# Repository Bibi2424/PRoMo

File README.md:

# PRoMo

## "Plateforme pour la Robotique Mobile"

### Mobile Robotic Plateform

This project is about creating a mobile robot from scratch.
There are four major parts in this project :

- Mechanics : Build a differential drive plateform with two DC motors with encoders. The different components must be build with Laser cutting and 3D printing (from low cost websites).
			
- Electronics : Create a main board based on a STM32F4 microcontroller with many components like motors, sensors, actuators, RF transmitters...
			
- Firmware : This can go two ways:
	- Provide a sets of high level librairies for controlling a sets of sensors and actuators and example projects, 
	- Give the code as is but with a performant way of interfacing with it (serial communication)

- Documentation : All the informations to understand the project will be there, with some tutorials. At the moment, used to store local datasheets
			
The aim of this projects is to propose some basics to start mobile robotic for the beginners and to simplify things for advanced people.

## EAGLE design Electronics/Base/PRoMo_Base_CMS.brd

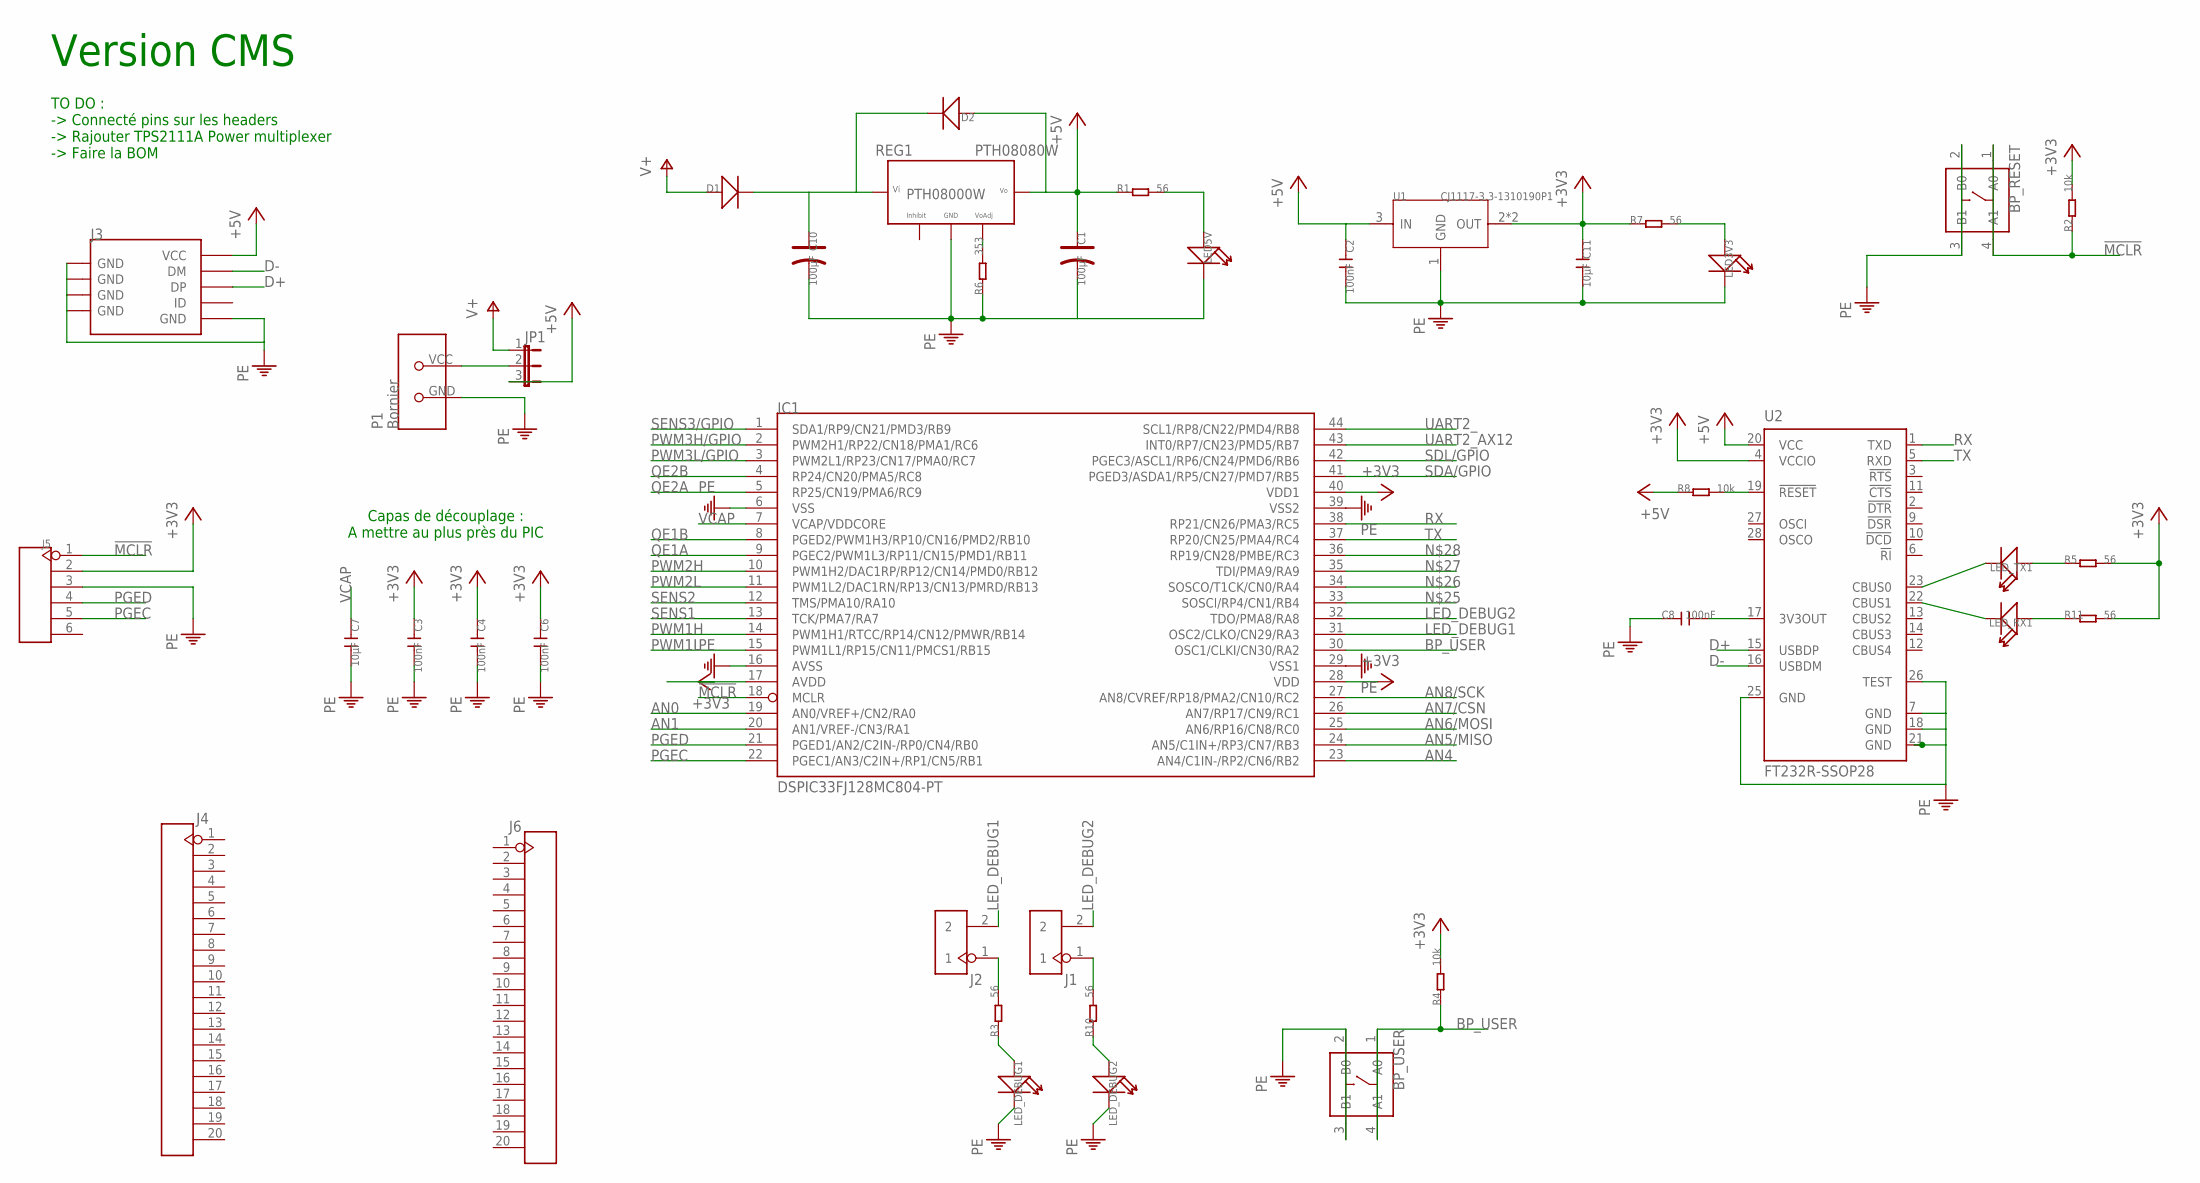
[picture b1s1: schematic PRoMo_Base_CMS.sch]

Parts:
BP_RESET: BUTTON-4P-6.2X6.2; 4P-6.2X6.2
BP_USER: BUTTON-4P-6.2X6.2; 4P-6.2X6.2
C1, C10: 100µF; ELECTRO-5.3MM
C2, C3, C4, C6, C8: 100nF; C1206
C7, C11: 10µF; C1206
D1, D2: D'DO-214AB'; DO-214AB
IC1: DSPIC33FJ128MC804-PT; TQFP44
J1, J2: HEADER-2P-65/35MIL; 2P-2.54-65/35MIL
J3: USB-MINIUSB-5P-TH; MINI-5P
J4, J6: HEADER-20P-2.54; 20P-2.54
J5: HEADER-6P-60/35MIL; 6P-2.54-60/35MIL
JP1: JP2E; JP2
LED3V3, LED5V: LED'1206'; LED-1206
LED_DEBUG1, LED_DEBUG2: LED'1206'; LED-1206
LED_RX1: LED'1206'; LED-1206
LED_TX1: LED'1206'; LED-1206
P1: Bornier; BORNIER_COUDEE_3.5
R1, R3, R5, R7, R10, R11: 56; R1206
R2, R4, R8: 10k; R1206
R6: 353; R0204/7
REG1: PTH08080W
U1: CJ1117-3.3-1310190P1; SOT223
U2: FT232R-SSOP28; SSOP28

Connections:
!MCLR!: BP_RESET.1 (A0), BP_RESET.4 (A1), IC1.18 (MCLR), J5.1, R2.1
+3V3: C3.1, C4.1, C6.1, C11.1, IC1.17 (AVDD), IC1.28 (VDD), IC1.40 (VDD1), J5.2, R2.2, R4.2, R5.2, R7.1, R11.2, U1.2 (OUT), U1.TER (OUT), U2.4 (VCCIO)
+5V: C1.+, C2.1, D2.1 (+), J3.VCC, JP1.3, R1.1, R8.1, REG1.P$5 (5_VO), U1.3 (IN), U2.20 (VCC)
AN0: IC1.19 (AN0/VREF+/CN2/RA0)
AN1: IC1.20 (AN1/VREF-/CN3/RA1)
AN4: IC1.23 (AN4/C1IN-/RP2/CN6/RB2)
AN5/MISO: IC1.24 (AN5/C1IN+/RP3/CN7/RB3)
AN6/MOSI: IC1.25 (AN6/RP16/CN8/RC0)
AN7/CSN: IC1.26 (AN7/RP17/CN9/RC1)
AN8/SCK: IC1.27 (AN8/CVREF/RP18/PMA2/CN10/RC2)
BP_USER: BP_USER.1 (A0), BP_USER.4 (A1), IC1.30 (OSC1/CLKI/CN30/RA2), R4.1
D+: J3.DP, U2.15 (USBDP)
D-: J3.DM, U2.16 (USBDM)
LED_DEBUG1: IC1.31 (OSC2/CLKO/CN29/RA3), J2.2
LED_DEBUG2: IC1.32 (TDO/PMA8/RA8), J1.2
unnamed: C10.+, D1.2 (-), D2.2 (-), REG1.P$1 (1_VI)
unnamed: R6.2, REG1.P$4 (4_VOADJ)
unnamed: LED5V.+, R1.2
unnamed: JP1.2, P1.VCC
unnamed: LED_DEBUG1.+, R3.1
unnamed: J2.1, R3.2
unnamed: LED3V3.+, R7.2
unnamed: C8.2, U2.17 (3V3OUT)
unnamed: R8.2, U2.19 (!RESET)
unnamed: LED_DEBUG2.+, R10.1
unnamed: LED_TX1.-, U2.23 (CBUS0)
unnamed: J1.1, R10.2
unnamed: LED_TX1.+, R5.1
unnamed: LED_RX1.+, R11.1
unnamed: LED_RX1.-, U2.22 (CBUS1)
PE: BP_RESET.2 (B0), BP_RESET.3 (B1), BP_USER.2 (B0), BP_USER.3 (B1), C1.-, C2.2, C3.2, C4.2, C6.2, C7.2, C8.1, C10.-, C11.2, IC1.6 (VSS), IC1.16 (AVSS), IC1.29 (VSS1), IC1.39 (VSS2), J3.GND, J3.S1 (GND), J3.S2 (GND), J3.S3 (GND), J3.S4 (GND), J5.3, LED3V3.-, LED5V.-, LED_DEBUG1.-, LED_DEBUG2.-, P1.GND, R6.1, REG1.P$3 (3_GND), U1.1 (GND), U2.7 (GND), U2.18 (GND), U2.21 (GND), U2.25 (GND), U2.26 (TEST)
PGEC: IC1.22 (PGEC1/AN3/C2IN+/RP1/CN5/RB1), J5.5
PGED: IC1.21 (PGED1/AN2/C2IN-/RP0/CN4/RB0), J5.4
PWM1H: IC1.14 (PWM1H1/RTCC/RP14/CN12/PMWR/RB14)
PWM1L: IC1.15 (PWM1L1/RP15/CN11/PMCS1/RB15)
PWM2H: IC1.10 (PWM1H2/DAC1RP/RP12/CN14/PMD0/RB12)
PWM2L: IC1.11 (PWM1L2/DAC1RN/RP13/CN13/PMRD/RB13)
PWM3H/GPIO: IC1.2 (PWM2H1/RP22/CN18/PMA1/RC6)
PWM3L/GPIO: IC1.3 (PWM2L1/RP23/CN17/PMA0/RC7)
QE1A: IC1.9 (PGEC2/PWM1L3/RP11/CN15/PMD1/RB11)
QE1B: IC1.8 (PGED2/PWM1H3/RP10/CN16/PMD2/RB10)
QE2A: IC1.5 (RP25/CN19/PMA6/RC9)
QE2B: IC1.4 (RP24/CN20/PMA5/RC8)
RX: IC1.38 (RP21/CN26/PMA3/RC5), U2.1 (TXD)
SDA/GPIO: IC1.41 (PGED3/ASDA1/RP5/CN27/PMD7/RB5)
SDL/GPIO: IC1.42 (PGEC3/ASCL1/RP6/CN24/PMD6/RB6)
SENS1: IC1.13 (TCK/PMA7/RA7)
SENS2: IC1.12 (TMS/PMA10/RA10)
SENS3/GPIO: IC1.1 (SDA1/RP9/CN21/PMD3/RB9)
TX: IC1.37 (RP20/CN25/PMA4/RC4), U2.5 (RXD)
UART2_: IC1.44 (SCL1/RP8/CN22/PMD4/RB8)
UART2_AX12: IC1.43 (INT0/RP7/CN23/PMD5/RB7)
V+: D1.1 (+), JP1.1
VCAP: C7.1, IC1.7 (VCAP/VDDCORE)

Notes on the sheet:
Version CMS
TO DO : -> Connecté pins sur les headers -> Rajouter TPS2111A Power multiplexer -> Faire la BOM
Capas de découplage : A mettre au plus près du PIC

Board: 4 copper layers, 41 parts (0 on the bottom side), 30 nets, no tracks yet.

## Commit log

2013-09-22 Premier commit : Ajout des ressources
    Ce premier commit consiste a rassembler tous les documents concernant ce
    projet.
2013-09-22 Avancement de la carte de base
2013-10-01 Choix des pins et début du routage
2014-06-18 Utilisation Lib SeeedStudio
2014-06-21 Schématique OK, début routage
2015-06-01 Routage done, mais revoir schématique
2016-11-15 Clean Up and Add start for 3D
2016-11-15 Finish cleaning and add create base for Eagle files
2018-10-27 Switch for PIC to ARM, basic project start
    Based on STM32F411RE Nucleo board, basic functions and basic encoder
    code working
2018-10-27 Give some love to this old project, re-define the scope of it
2018-10-28 Add motor basic support, switch to proto shield
2018-10-31 Improve Makefile and basic UART rx
2020-10-27 Move to Kicad and schematic Design almost done
2020-11-01 Schematic update and placement DONE
2020-11-07 Routing Done, All files ready for ordering
2020-11-20 Prepare Electronics v0.2, Add ballcaster holder file
2021-02-14 Small update to schematic and todo
2021-02-20 Remove Firmware code from main repo, will be added as submodule
2021-02-20 Add back the Firmware from submodule
2021-02-20 Some cleanup on the README
2021-02-23 Update License to MIT
2021-02-23 Bring Firmware up to speed
2021-02-23 Update firmware
2021-09-11 Start working on HW v0.2
2022-03-05 Update firmware submodule
2025-02-23 Update fw
